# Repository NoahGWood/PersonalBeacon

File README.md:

# PersonalBeacon
Personal Beacon is a key-fob sized emergency radio beacon designed to enable the location of persons trapped inside collapsed structures. While cell phones and common walkie-talkies may not be in reach during an emergency or able to make it through rubble, this beacon is small enough to carry on a keychain and utilizes the same frequencies as ground-penetrating radar allowing for one-way communication from the rubble to rescuers above.

## Why Was This Device Created?

This device was created in response to the tragedies caused by the Western Kentucky tornado where dozens of people were trapped under buildings, cars, under other debris and were unable to be recovered in time due to the inability of first responders to locate victims in the rubble.

## How It Works

When activated the personal beacon sends out an FM ping on the 30MHz frequency once per second. The beacon uses a low wattage transmitter (~1/2 watt) which operates on the police/emergency band in the U.S. (30MHz) allowing the signal to be picked up by standard issue radios. The strength of the signal is directly proportional to the distance between the receiver and beacon allowing for first responders to use their handheld radios to quickly triangulate the position of the beacon by the change in volume of the ping.

In addition to the beacon, the device embeds a MEMS microphone and a push-to-talk button enabling one-way communication from the entrapped person.

## How Long Does The Beacon Last?

The original design utilizes a pair of CR2477 batteries. The battery life is dependent on which mode the beacon is currently operating in.

### Standby Mode

Standby mode is the default mode, the microprocessor on the beacon is silently waiting for the wake-up command (on button). In standby mode, the estimated lifespan of the device is 8 years allowing you to daily carry the device without worrying about charging it. It is still recommended to replace the batteries every 3-4 years to ensure enough charge in event you need to use the beacon.

### Beacon Only

Beacon only mode is the default mode of the beacon after activation. During this time, the beacon will send out an audible pulse over the radio once per second. The beacon is expected to continue pinging for up to 17 days.

### Push To Talk

Push-to-talk mode is the mode that is entered while holding down the PTT button. The PTT mode drains the battery much faster than the beacon mode as it runs the transmitter the entire time the PTT button is held down. 

to last up to 17 days. During push-to-talk mode the device can be expected to last 12-24 hours. Additionally, charging circuitry is available for a larger (pocket-clipped) lithium-ion based beacons. The beacon is a very low wattage transmitter (~1/2 watt) which operates on the police/emergency band in the U.S. (30MHz) allowing the signal to be picked up by a handheld radio. The volume of the audible beacon on the receiver is directly proportional to the distance between the receiver and the beacon allowing first responders to use their handheld as effective dousing rods to locate entrapped persons.

## How Should This Device Be Used?

This device should be carried on your person at all times in an easy-to-reach place. In the event you become lost, stuck, or otherwise need emergency assistance (as in the case of entrapment) and you are unable to reach emergency services by any other means, you should activate beacon mode by pressing the emergency button once. It is then recommended that you use the PTT feature to send a short transmission declaring a "mayday" (international distress signal), identifying yourself, any injuries you may have, your last known location within the building, and any other pertinent information that may be beneficial to your rescue. It is recommended that you provide sparing, but repeated updates as to the situation until your rescue. Upon rescue be sure to deactivate the beacon by pressing the emergency button again, if the device fails to shut off for any reason you can simply remove the battery.

A typical emergency broadcast is structured as follows:

**MAYDAY, MAYDAY, MAYDAY**
**THIS IS** (your name)
**My location is** (address)
**I AM** (trapped, etc.)
**I REQUIRE IMMEDIATE ASSISTANCE**
**I HAVE** (number of people with you, injuries, other pertinent info)
**OVER**

An example might be:

> "Mayday, mayday, mayday, this is Noah Wood, I am trapped in building 1 at St. Johns and cannot escape. I am trapped in the waiting area there are 5 people with me, we have injured. Unable to receive. I have activated a radio beacon. OUT"

"OUT" was used in place of "OVER" as the device does not currently implement a receiver to allow two-way communications.

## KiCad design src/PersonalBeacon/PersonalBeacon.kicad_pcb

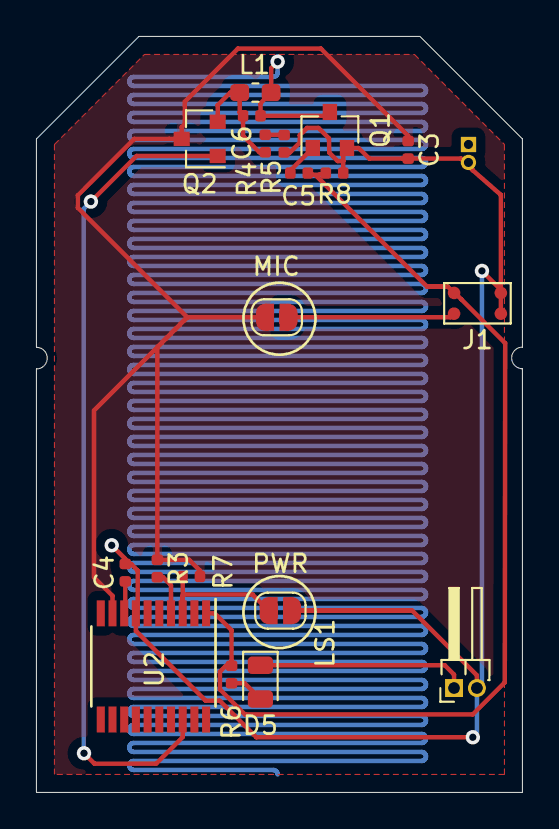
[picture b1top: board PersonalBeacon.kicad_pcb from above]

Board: 2 copper layers, 27.0 x 42.0 mm, 20 parts (1 on the bottom side), 14 nets.

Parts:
BT1: Battery_Cell; PinHeader_1x02_P1.00mm_Vertical
C3: 100nF; C_0402_1005Metric
C4: 1uF; C_0402_1005Metric
C5: 330nF; C_0402_1005Metric
C6: 281pF; C_0402_1005Metric
D5: BeepLED; LED_0805_2012Metric
J1: MEMS Microphone; MEMS_MIC
L1: 100nH; L_0603_1608Metric_Pad1.05x0.95mm_HandSolder
LS1: Speaker; PinHeader_1x02_P1.27mm_Horizontal
MIC: PTT; SolderJumper-2_P1.3mm_Open_RoundedPad1.0x1.5mm
PWR: PWR_ON; SolderJumper-2_P1.3mm_Open_RoundedPad1.0x1.5mm
Q1, Q2: Q_NPN_BEC; SOT-23
R3, R4, R5, R6, R7: 10k; R_0402_1005Metric
R8: 1K; R_0402_1005Metric
U2: STM8S003F3P; TSSOP-20_4.4x6.5mm_P0.65mm

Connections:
+3V3: C3.1, MIC.1, Q2.3, R3.1, R7.1, U2.9
GND: BT1.2, C3.2, C4.2, J1.2, J1.3, LS1.2, PWR.2, Q1.2, R5.1, R8.1, U2.7
IP: C5.2, J1.4, R6.1, R8.2, U2.1
unnamed: C6.1, L1.2, Q1.3
unnamed: C4.1, U2.8
unnamed: C5.1, Q1.1
unnamed: C6.2, L1.1, Q2.2, R4.1
unnamed: D5.1, LS1.1
unnamed: D5.2, R6.2
unnamed: J1.1, MIC.2
unnamed: R3.2, U2.4
unnamed: R4.2, R5.2
unnamed: PWR.1, R7.2, U2.3
Radio_On: Q2.1, U2.18

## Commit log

2021-12-16 modified: README.md new file: imgs/beacon1.png new file: imgs/beacon2.png new file: src/PersonalBeacon/PersonalBeacon-cache.lib new file: src/PersonalBeacon/PersonalBeacon.kicad_pcb new file: src/Per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

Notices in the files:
src/PersonalBeacon/PersonalBeacon.kicad_pcb:
(c) 2021
